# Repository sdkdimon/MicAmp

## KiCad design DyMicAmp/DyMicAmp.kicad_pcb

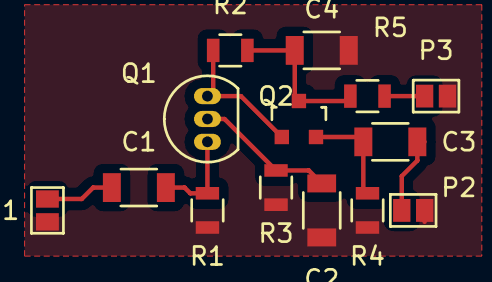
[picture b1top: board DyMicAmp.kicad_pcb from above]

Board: 2 copper layers, 14 parts (0 on the bottom side), 9 nets.

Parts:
C1, C3: C_1206
C2: ddwdad; C_1206
C4: CP_Small; C_1206
P1: Input; GS2
P2: Output; GS2
P3: VC; GS2
Q1: BF245A; TO-92_Inline_Narrow_Oval
Q2: BC817-25; SOT-23
R1, R2, R5: R_0805
R3, R4: R_Small; R_0805

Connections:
unnamed: C1.1, P1.1
unnamed: C1.2, Q1.1, R1.1
unnamed: C2.1, Q1.2, R3.1
unnamed: C2.2, C4.2, P1.2, P2.2, P3.2, R1.2, R3.2, R4.2
unnamed: C3.1, P2.1
unnamed: C3.2, Q2.2, R4.1
unnamed: C4.1, Q2.3, R2.1, R5.2
unnamed: P3.1, R5.1
unnamed: Q1.3, Q2.1, R2.2
